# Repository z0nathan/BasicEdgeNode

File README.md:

# BEN — Basic Edge Node

## Main Differences

> **RoBoHoN actuator variant**, contributed by [@slightly-engineered](https://github.com/slightly-engineered).
> BEN can also be built with two **RoBoHoN (Sharp SR01M) elbow actuators** (Orbray BLDC serial-bus servos)
> instead of the DM-S0020 PWM micro servos. Everything RoBoHoN-specific is listed below; the
> PWM examples are unchanged.

## Variant: BEN with RoBoHoN actuators

*Viewed from the back of the robot. Left and right in all of this variant's notes mean as seen in this photo.*

| Change from the standard build | Details | Files |
|---|---|---|
| **Actuators** | Two RoBoHoN elbow actuators on RoBoHoN's serial bus (115200 baud, 3.7 V) | [`firmware/examples/webCamMotionRobohon/`](firmware/examples/webCamMotionRobohon/) |
| **Neck brackets** | The ball on the neck side of each bracket is scaled to **90%**. At full size it was too tight in the neck socket: too much friction, and brackets snapped. These were printed in resin, which likely holds tighter tolerances than FDM/PLA. | [`hardware/robohon-variant/`](hardware/robohon-variant/) |
| **Eyes** | Two **5 mm through-hole LEDs** instead of the FPCB's surface-mount LEDs. The neck has two slots for them. | `neck.stl`, `5mmLED_v2.stl` |
| **Head button** | The Kailh Choc switch is **removed**. The neck is modified so the head clips straight on. | `neck.stl` |

### Wiring at a glance

| Side (viewed from the back) | Actuator | Bus ID |
|---|---|---|
| **Left** | RoBoHoN **left elbow** | SID 4 |
| **Right** | RoBoHoN **right elbow** | SID 5 |

The firmware sends the same bus frames on **GPIO 4 and GPIO 5**, so either actuator's data
wire can go to either servo pad. Each actuator only obeys its own ID: what matters is that
the **left elbow actuator is on the left** and the **right elbow actuator is on the right**.
Power the actuators from a 1S Li-ion/LiPo (3.7 V), not BEN's 5 V pad, with the battery
negative tied to BEN's GND.

### Upload and test

1. Build and flash [`firmware/examples/webCamMotionRobohon/`](firmware/examples/webCamMotionRobohon/) with ESP-IDF 5.3 or newer.
2. With the arms or links off, hold both actuators at home:
   `python webcam_bridge.py --port <your COM port> --home-only` (run from `firmware/examples/webCamMotion/`).
   Fit both arms vertical, then press Ctrl+C to release.
3. Run the bridge normally and look straight at the camera. Both arms should rotate about
   20 degrees **outward**, away from each other. If one rotates inward, flip that side's
   `LEFT_DIR` / `RIGHT_DIR` in `main/main.c` and rebuild.

Full details: [`firmware/examples/webCamMotionRobohon/README.md`](firmware/examples/webCamMotionRobohon/README.md).

---

**A minimal desktop companion robotics platform.**

BEN is a small desktop robot built around a simple idea: how far can a desktop companion be simplified while still remaining expressive?

It keeps only the essentials:

- 2 DOF
- Single-button input
- USB-powered
- LED eyes and heart

Design files are provided as-is. Feel free to build on them, modify them, or just poke around.

## Hardware

BEN is built around an **ESP32-C3 SuperMini** and a custom flexible PCB (FPCB).

| Component          | Specification                    |
| ------------------ | -------------------------------- |
| MCU                | ESP32-C3 SuperMini               |
| Degrees of freedom | 2 DOF (roll&pitch)                           |
| Actuators          | 2 × DM-S0020 2g micro servo      |
| Input              | 1 × Kailh Choc V2 mechanical switch |
| LEDs | 3 × LUXEON 3535L LED    |
| Power              | 5 V USB C                         |
| PCB                | Custom FPCB                      |
| Mechanical parts   | 3D printed                       |

The two servos provide the neck motion, while the three LEDs provide simple visual expression.

The button on top of the head acts as BEN's primary physical input.

## Pinout

| Function             | ESP32-C3        |
| -------------------- | --------------- |
| Left / Right Eye LED | GPIO 0 / GPIO 3 |
| Heart LED            | GPIO 1          |
| Servo 1              | GPIO 4          |
| Servo 2              | GPIO 5          |
| Head Button          | GPIO 10         |
| Servo Power          | 5 V             |
| Logic Power          | 3.3 V           |
| Common Ground        | GND             |

The LEDs are connected through current-limiting resistors and can be brightness-controlled using PWM.

## Electronics

The complete editable electronics design is provided as a KiCad project:

```text
BEN.kicad_pro
BEN.kicad_sch
BEN.kicad_pcb
```

The files were converted and verified using **KiCad 9**.

The FPCB integrates the controller, LED connections, servo connections, and button interface into a single compact board designed to fit inside BEN.

## Mechanical Design

BEN uses a compact 2-DOF neck mechanism driven by two micro servos.

The mechanism was designed to minimize the number of actuators and mechanical components while still allowing expressive head movement.

STEP files are provided for modification and fabrication.

## Building BEN

### Electronics

Open:

```text
hardware/electronics/BEN.kicad_pro
```

The provided `.kicad_sch` and `.kicad_pcb` files contain the editable schematic and PCB design.

### Mechanical Parts

STEP file is provided under:

```text
hardware/CAD/
```

They can be modified in most CAD software or used to generate files for 3D printing.

### Firmware

The original button-triggered hardware test is provided as a standalone
ESP-IDF project in [`firmware/examples/internalTest/`](firmware/examples/internalTest/). Its local README contains
build, flash, and legacy test-pin instructions.

The [`firmware/examples/webCamMotion/`](firmware/examples/webCamMotion/)
example follows webcam head pitch and roll while laptop audio controls eye
brightness.

The [`firmware/examples/webCamMotionRobohon/`](firmware/examples/webCamMotionRobohon/)
example runs the same webcam bridge with two RoBoHoN elbow bus servos in place
of the DM-S0020 micro servos.

Feel free to modify it, add new behaviors, or use BEN as a platform for your own desktop robotics experiments.

## Building guide

A step-by-step build guide, including fabrication, assembly, wiring, and setup, is available on Instructables:
 [Instructables](https://www.instructables.com/BEN-Your-Minimal-Desktop-Companion/)

## Third-Party Resources

The project uses the following third-party resources:

* **Kailh Choc switch footprint** — [KiSwitch](https://github.com/kiswitch/kiswitch/tree/main/library/footprints/Switch_Keyboard_Kailh.pretty)
* **ESP32-C3 SuperMini symbol/footprint** — [SnapMagic / SnapEDA](https://www.snapeda.com/parts/ESP32-C3%20SuperMini_TH/Espressif%20Systems/view-part/)
* **ESP-IDF** — [Espressif IoT Development Framework](https://github.com/espressif/esp-idf), used to build the example firmware and distributed under the Apache License 2.0.
* **MediaPipe** — [Google MediaPipe](https://github.com/google-ai-edge/mediapipe), used for webcam face landmarks under the Apache License 2.0.
* **OpenCV** — [OpenCV](https://opencv.org/), used for camera capture and head-pose geometry under the Apache License 2.0.
* **NumPy** — [NumPy](https://numpy.org/), used for pose and audio calculations in the webcam bridge.
* **SoundCard** — [SoundCard](https://github.com/bastibe/SoundCard), used to capture laptop output or microphone audio.
* **pySerial** — [pySerial](https://github.com/pyserial/pyserial), used for the laptop-to-ESP32 connection.
* **pynput** — [pynput](https://github.com/moses-palmer/pynput), used to convert the physical switch event into a Space key press.

These resources remain subject to their respective original licenses and terms.

## License

BEN uses separate licenses for hardware and software.

### Hardware

CAD files, schematics, PCB designs, and other hardware design files are licensed under the **CERN Open Hardware Licence Version 2 — Weakly Reciprocal (CERN-OHL-W-2.0)**.

Commercial use and modification are allowed under the terms of the license.

See `LICENSE-HARDWARE` for details.

### Software

Firmware and software are licensed under the **MIT License**.

Commercial use and modification are allowed under the terms of the license.

See `LICENSE-SOFTWARE` for details.

---

## Community

Built something with BEN?

If you modify the hardware, develop a new behavior, or use BEN in another project, I'd love to see what you come up with.

Feel free to open an issue, submit a pull request, or share your build. Interesting modifications and projects may be featured here in the future.

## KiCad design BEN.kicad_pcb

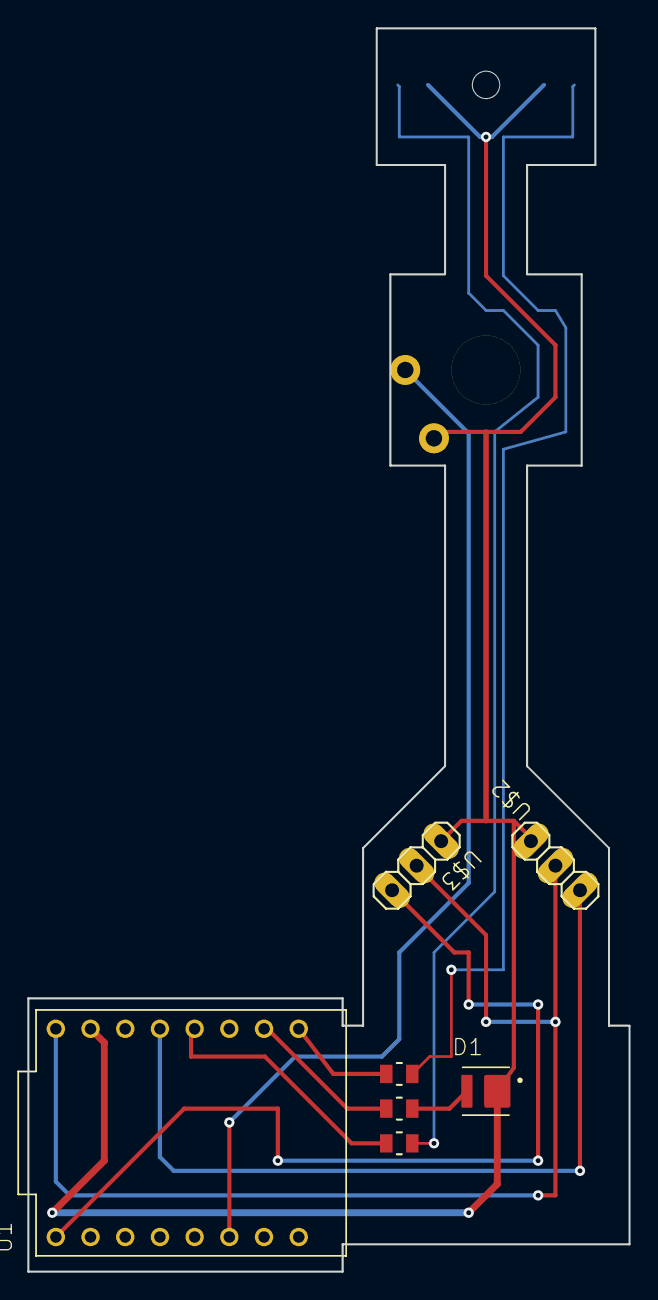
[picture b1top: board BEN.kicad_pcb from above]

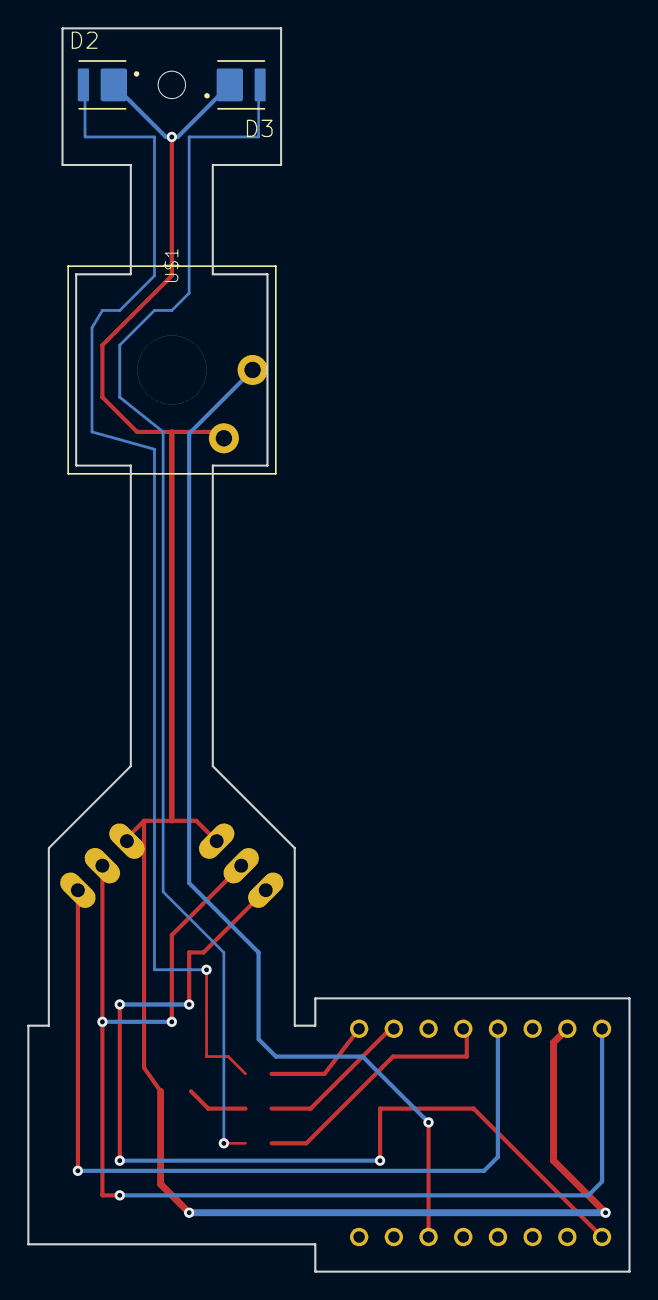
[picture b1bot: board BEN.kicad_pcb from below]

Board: 2 copper layers, 44.0 x 91.0 mm, 11 parts (3 on the bottom side), 11 nets.

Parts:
D1, D2, D3: L135-A589003500000; LED_L135-A589003500000_vf.D1ZenvC7SHGpa8JOMR4Mzw
R1, R2, R3: RC0805FR-07220RLRES_RC0805_YAG; RES_RC0805_YAG_vf.D1ZenvC7SHGpa8JOMR4Mzw
U1: ESP32-C3_SUPERMINI_TH; MODULE_ESP32-C3_SUPERMINI_TH_vf.D1ZenvC7SHGpa8JOMR4Mzw
U$1: CHOC_V2_CPTSW_KAILH_CHOC_V1V2_1.00U; SW_KAILH_CHOC_V1V2_1.00U_vf.D1ZenvC7SHGpa8JOMR4Mzw
U$2, U$3: SERVOSG90-HDR; 1X03_30890021
UNK_HOLE_0: dummyfp0

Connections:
unnamed: D1.A, R1.2
unnamed: D2.A, R2.2
unnamed: D3.A, R3.2
unnamed: D1.C, D2.C, D3.C, U1.G, U$1.2, U$2.1, U$3.1
unnamed: U1.5V, U$2.2, U$3.2
unnamed: U1.4, U$2.3
unnamed: U1.5, U$3.3
unnamed: U1.10, U$1.1
unnamed: R1.1, U1.1
unnamed: R2.1, U1.0
unnamed: R3.1, U1.3
